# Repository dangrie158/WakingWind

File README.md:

WakingWind
==========

>“Waking Wind” is a webservice with realtime weatherdata for windsportmen. The slogan “real-time wind data from anywhere to everywhere” describes the focus of easy data retrieval even from the most abandoned places as well as the easy access to the data on-the-go.

This project was created during the summer semester 2013 at the Hochschule der Medien in Stuttgart. I created this project together with my fellow student Thorsten Schaeff.

Our goal was it to create a realtime weather service for wind sportsmen in egypt. Often, these people live far away from the surf spot without access to accurate wind speed data.

The final product features the outside station of a cheap weather station, the custom receiver, a RaspberryPi to collect the data and send it to the Webserver, a Website and a Mobile App for Android that let you set an Alarm and notifies you as soon as the windspeed exceeds a set threshold.

Waking Wind von Daniel Grießhaber <dangrie159@gmail.com>, Thorsten Schaeff <thorsten@schaeffonline.com> is Licenced under the MIT Licence. For more information see NOTICE File.

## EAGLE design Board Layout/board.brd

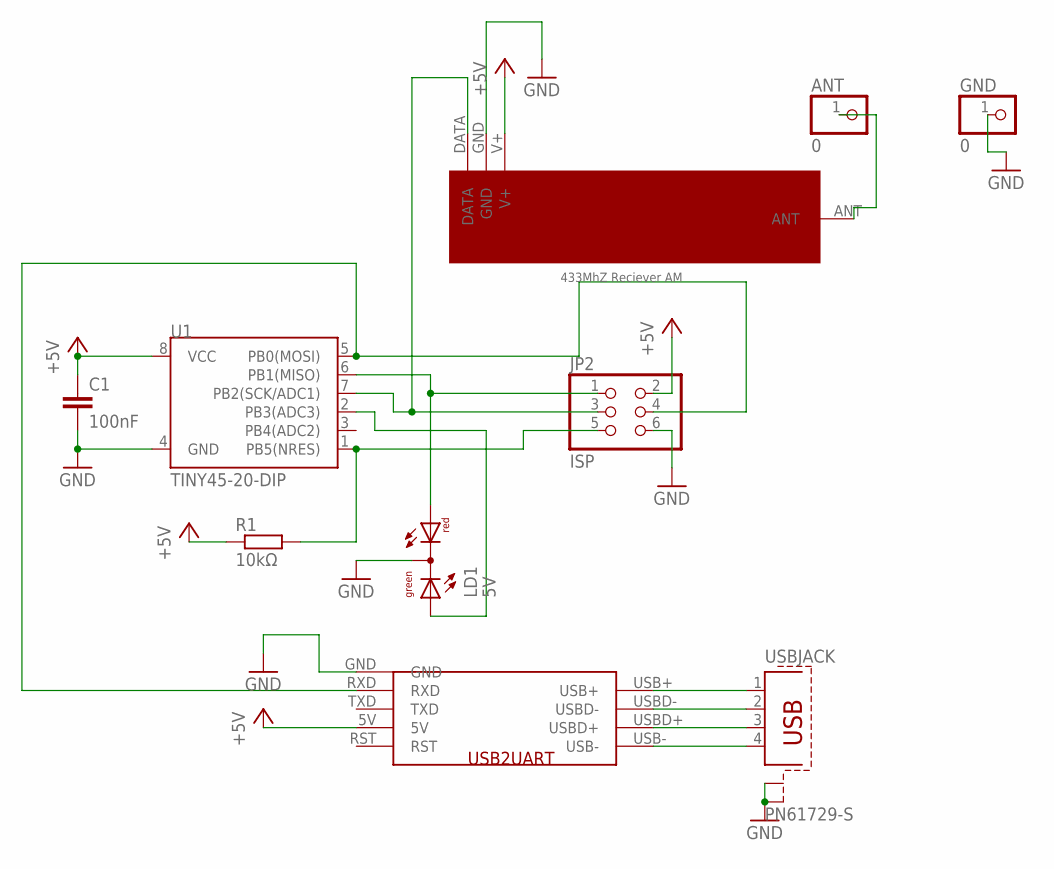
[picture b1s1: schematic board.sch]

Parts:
ANT: 0; 1X01
C1: 100nF; C050-024X044
GND: 0; 1X01
JP2: ISP; 2X03
LD1: 5V; DUOLED-C-5MM
R1: 10kΩ; 0411/15
U1: TINY45-20-DIP; DIP08
U$1: USB2UART
U$2: 433MHZREC
USBJACK: PN61729-S

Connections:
+5V: C1.1, JP2.2, R1.1, U1.8 (VCC), U$1.5V, U$2.V+
ANT: ANT.1, U$2.ANT
GND: C1.2, GND.1, JP2.6, LD1.C, U1.4 (GND), U$1.GND, U$2.GND, USBJACK.S1, USBJACK.S2
unnamed: JP2.4, U1.5 (PB0(MOSI)), U$1.RXD
unnamed: JP2.3, U1.7 (PB2(SCK/ADC1)), U$2.DATA
unnamed: JP2.1, LD1.AR, U1.6 (PB1(MISO))
unnamed: LD1.AX (AG), U1.2 (PB3(ADC3))
unnamed: JP2.5, R1.2, U1.1 (PB5(NRES))
unnamed: U$1.USB+, USBJACK.1
unnamed: U$1.USBD-, USBJACK.2
unnamed: U$1.USBD+, USBJACK.3
unnamed: U$1.USB-, USBJACK.4

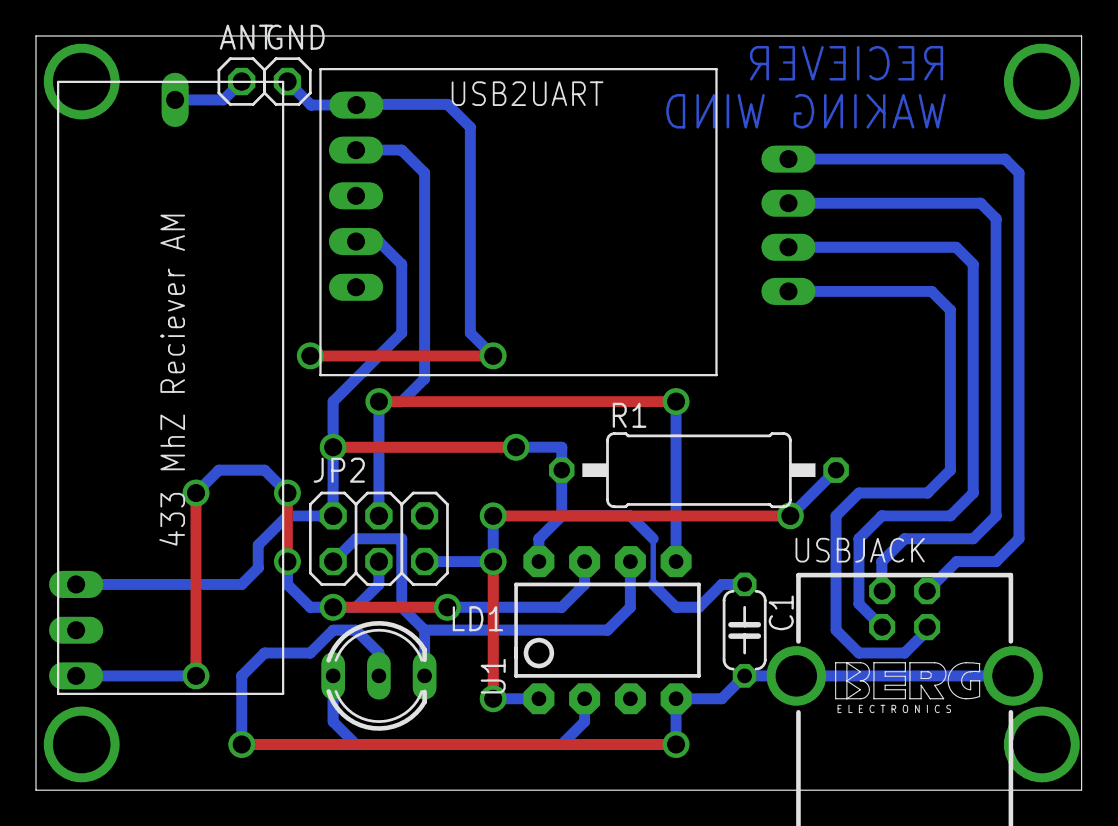
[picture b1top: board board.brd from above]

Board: 2 copper layers, 58.1 x 41.9 mm, 10 parts (0 on the bottom side), 12 nets.

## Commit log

2014-06-23 Added MIT Licence
2014-06-23 moved some Files
2014-06-23 cleanup Website files
2014-06-23 removed old Website Version
2014-06-23 remove precompiled pdf files

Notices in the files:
parts and their libraries:
SparkFun-DigitalIC: Licensing: CC v3.0 Share-Alike You are welcome to use this library for commercial purposes.
